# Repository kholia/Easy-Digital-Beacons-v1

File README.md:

### Easy-Digital-Beacons-v1

A simple and easy WiFi-enabled ESP8266-powered WSPR, FT8, and FT4 beacon system
which uses NTP + DS3231 RTC for timing. Also, checkout our [cost-effective, and
robust HF 5W PA system](https://github.com/kholia/HF-PA-v5/).

It is also a WiFi-enabled VFO, which is quite useful, and convenient for radio
experimentation work.

Note: The whole project can be assembled on a breadboard (including the [250mW
amplifier](./QRPp-Amplifier)) in under 30 minutes - do give it a go ;)

The whole design is modular, parametric (cost and others), field repairable,
and super extensible. It is almost trivial to add support for more `beacon
modes`.

#### Build Steps

If you are using Windows OS, execute the following steps:

- Download this repository by [clicking here](https://github.com/kholia/Easy-Digital-Beacons-v1/archive/refs/heads/master.zip).

- Extract the downloaded zip file to a folder.

- Run the `setup_arduino_ide.bat` file inside this folder.

- Install https://github.com/me-no-dev/ESPAsyncWebServer library.

- Install https://github.com/me-no-dev/ESPAsyncTCP library.

If you are on Linux, execute the following steps:

```
sudo apt-get install git  # install 'git' if needed

git clone https://github.com/kholia/Easy-Digital-Beacons-v1.git

make install_arduino_cli
make install_platform
make deps  # using Windows?, read the 'Makefile' file

cd ~/Arduino/libraries
git clone https://github.com/me-no-dev/ESPAsyncWebServer.git
git clone https://github.com/me-no-dev/ESPAsyncTCP.git
```

Now execute these common steps:

Add your WiFi credentials in `Easy-Digital-Beacons-v4/credentials.h` file

Change the following lines in the code to use your values:

```
char message[] = "VU3CER VU3FOE MK68";
char call[] = "VU3FOE";
char loc[] = "MK68";
uint8_t dbm = 27;
```

[OPTIONAL] Change the following line in the code to suit your Si5351A module:

```
int32_t si5351CalibrationFactor =  ...
```

Use [this program](https://github.com/etherkit/Si5351Arduino/blob/master/examples/si5351_calibration/si5351_calibration.ino)
to derive the calibration value for your Si5351A module.

Follow [this tutorial first](https://randomnerdtutorials.com/esp8266-web-server-spiffs-nodemcu/) to
get familiar with `SPIFFS` uploading stuff. Use the `Tools -> ESP8266 Sketch
Data Upload` option in the Arduino IDE to upload the webserver resources to
ESP8266. Note: The webserver resources are located in the `data` folder
inside the `Easy-Digital-Beacons-v4` sketch.

Open and upload the `Easy-Digital-Beacons-v4` sketch to ESP8266 using the
`Sketch -> Upload` option in the Arduino IDE.

You are all set for the next step - congrats!

#### Usage

Turn off the `SW1` switch, and reboot the beacon system. The beacon system now
connects to your WiFi, and then runs a web server.

This web server can be accessed at http://beacon.local URL typically.

Beacon's web interface:

Use this web interface to configure the beacon. Please use the `NTP Sync`
option in this web interface to set the RTC time fairly correctly.

Now, turn on the `SW1` switch, and reboot the beacon system. The beacon system
is active now, and will TX as per the configuration.

TIP: Please use a local (or nearby) receiver to receive and decode the beacon
signals! This is important to ensure that your beacon is TX'ing correctly.

Si5351A module is connected via I2C to pins D1 (SCL) and D2 (SDA) of the Wemos
D1 Mini board. Connect DS3231 similarly.

Here is the schematic for the `Easy-Digital-Beacons-v4` sketch:

For troubleshooting, you may want to try the following similar project by the
awesome WB2CBA:

- https://antrak.org.tr/blog/esp-wspr-simple-and-inexpensive-wspr-transmitter/
- https://antrak.org.tr/blog/a-whisper-wspr-adventure-and-esp_wspr/

#### Notes

Note 2 (March-2022): The `FT4` beacon is decently reliable now (all thanks to
Anupam).

Author: Dhiru Kholia (VU3CER) - https://www.qrz.com/db/VU3CER/

Author 2: Anupam Saikia - https://github.com/anupamsaikia

The `DT` timings are very nice with `NTP Sync`, `DS3231 RTC` and the optional
`time-delta hack`.

7W (or less) of HF RF power offers global communications coverage when
propagation is good:

WSPR mode demo:

Sample 3D rendering:

FT4 mode demo:

FST4W mode demo:

#### Battery System Recommendation

I recommend using a LiFePo4 (LFP) battery which has good energy density and is
also priced decently well.

Use the LFP battery with a `1S LFP BMS`.

The BMS' output can be connected directly to the 3.3v input of the ESP8266
module.

#### NTP (Time) Sync for FST4W-Antonio

In the Arduino IDE, select `Tools -> Serial Monitor`. In the `Serial Monitor`
send `s` character to ESP8266 to trigger the `NTP Time Sync` process.

Reboot ESP8266 to check if RTC is retaining the correct time. If not, change
the RTC battery.

#### Power Notes

This will need a HF RF PA in most cases to be usable on the air.

UPDATE (May 2022): Checkout our [cost-effective, and robust HF PA system](https://github.com/kholia/HF-PA-v6/).

You can also start with the easy-to-build and breadboard-friendly [QRPp-Amplifier](./QRPp-Amplifier).

#### Relay Usage

We use a 2-channel relay as a `T/R switch`.

See https://github.com/kholia/Simple-TR-Switch for details.

Also check out https://github.com/kholia/Easy-Transceiver project.

#### BOM

- 1 x 3/5mm LED (purple or pink is recommended)

- 1 x small regular (spst) chassis mount switch

- 1 x 0.25w 470 ohm resistor (CFR / MFR)

- Relimate male connectors

- Relimate female-female cables

- Female berg strips

- Zero PCB of a suitable size

Si5351A Module:

DS3231 RTC Module:

μC Board:

OLED screen (optional):

#### BOM Sources

- https://robu.in/

- https://www.electronicscomp.com/

- https://projectpoint.in/

#### Tips

Useful commands:

```
pacmd load-module module-null-sink sink_name=Virtual0
pacmd update-sink-proplist Virtual0 device.description=Virtual0
pacmd update-source-proplist Virtual0.monitor device.description=Virtual0
```

Use Gqrx and WSJT-X with a SDR device for initial frequency adjustment /
calibration. This is essential for WSPR functionality. FT8 is more
robust/tolerant of frequency deviations due to a much larger RX window.

Note: To customize the FST4W beacon to use your callsign and grid, use the
following commands to generate the `FST4Wsymbols` array data.

```
fst4sim.exe "IK1HGI JN45 20" 60 1500 0.0 0.1 1.0 10 -15 F > message.txt

message2array.exe message.txt
```

Replace the original `FST4Wsymbols` array data with the output of
`message2array.exe` program.

#### Future Tasks

- Change Si5351 calibration factor from the Web UI

- Add support for custom FT8 / FT4 messages

- Re-announce mDNS stuff [LP]

- EEPROM - save TX interval / schedule [LP]

- Reset to defaults button [LP]

#### References + Credits

- https://github.com/kholia/Si5351-Module-Clone-TCXO/ (use this module - it rocks!)

- https://github.com/kholia/Easy-Transceiver

- https://github.com/kgoba/ft8_lib

- https://github.com/etherkit/JTEncode

- https://github.com/Naguissa/uEEPROMLib

- https://randomnerdtutorials.com/esp8266-web-server-spiffs-nodemcu/

- https://lastminuteengineers.com/ds3231-rtc-arduino-tutorial/

- https://learn.adafruit.com/adafruit-si5351-clock-generator-breakout/wiring-and-test

- https://github.com/agustinmartino/wsjt_transceiver

- https://github.com/agustinmartino/wsjtx_transceiver_interface

- https://www.qrp-labs.com/synth/ms5351m.html

- https://github.com/anupamsaikia - FT4 fixes - thanks!

- https://github.com/f4goh/WSPR (pretty cool)

- https://github.com/lu7did/PixiePi

- https://github.com/iw5ejm/multibandWSPR_nodeMCU

- https://km4nmp.com/2019/08/24/vfo-for-the-pixie-wiring-and-sketch-for-ad9850/

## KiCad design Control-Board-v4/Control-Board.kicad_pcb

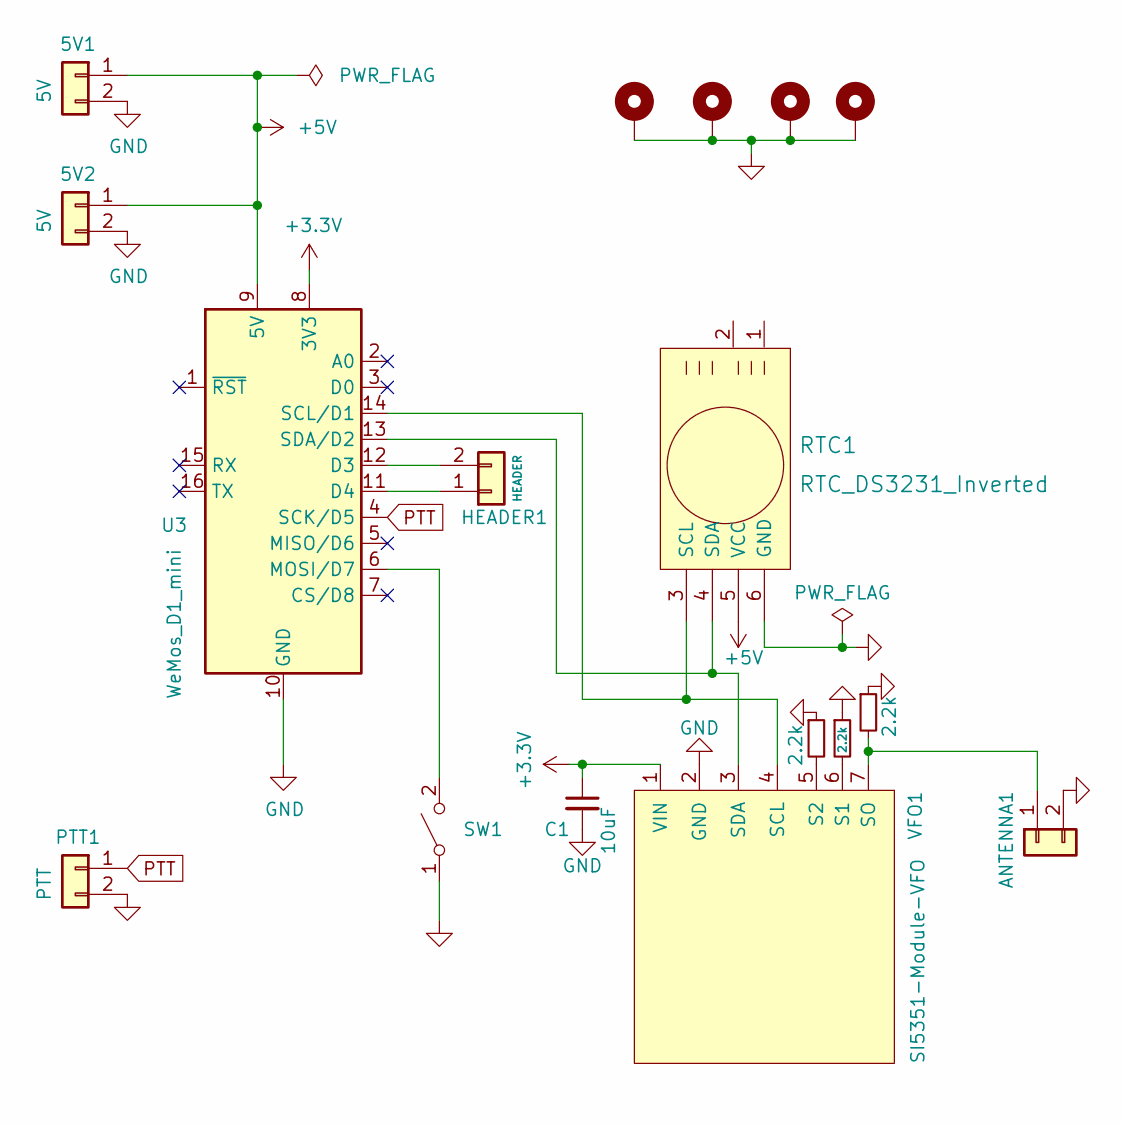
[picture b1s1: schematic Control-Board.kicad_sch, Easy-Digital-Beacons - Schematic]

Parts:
5V1, 5V2: 5V; PinHeader_1x02_P2.54mm_Vertical
ANTENNA1: ANTENNA; TerminalBlock_bornier-2_P5.08mm
C1: 10uF; C_1206_3216Metric_Pad1.33x1.80mm_HandSolder
H1, H2, H3, H4: MountingHole; MountingHole_2.2mm_M2_Pad
HEADER1: HEADER; PinHeader_1x02_P2.54mm_Vertical
PTT1: PTT; PinHeader_1x02_P2.54mm_Vertical
R1, R2, R3: 2.2k; R_1206_3216Metric_Pad1.30x1.75mm_HandSolder
RTC1: RTC_DS3231_Inverted; PinSocket_1x06_P2.54mm_Horizontal
SW1: SW_SPST; PinHeader_1x02_P2.54mm_Vertical
U3: WeMos_D1_mini; WEMOS_D1_mini_light
VFO1: SI5351-Module-VFO; PinSocket_1x07_P2.54mm_Vertical

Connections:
+3.3V: C1.1, U3.8 (3V3), VFO1.1 (VIN)
+5V: 5V1.1, 5V2.1, RTC1.5 (VCC), U3.9 (5V)
GND: 5V1.2, 5V2.2, ANTENNA1.2, C1.2, H1.1, H2.1, H3.1, H4.1, PTT1.2, R1.1, R2.1, R3.1, RTC1.6 (GND), SW1.1 (A), U3.10 (GND), VFO1.2 (GND)
unnamed: ANTENNA1.1, R3.2, VFO1.7 (SO)
unnamed: HEADER1.1, U3.11 (D4)
unnamed: HEADER1.2, U3.12 (D3)
unnamed: RTC1.3 (SCL), U3.14 (SCL/D1), VFO1.4 (SCL)
unnamed: RTC1.4 (SDA), U3.13 (SDA/D2), VFO1.3 (SDA)
unnamed: SW1.2 (B), U3.6 (MOSI/D7)
unnamed: R2.2, VFO1.6 (S1)
unnamed: R1.2, VFO1.5 (S2)
PTT: PTT1.1, U3.4 (SCK/D5)

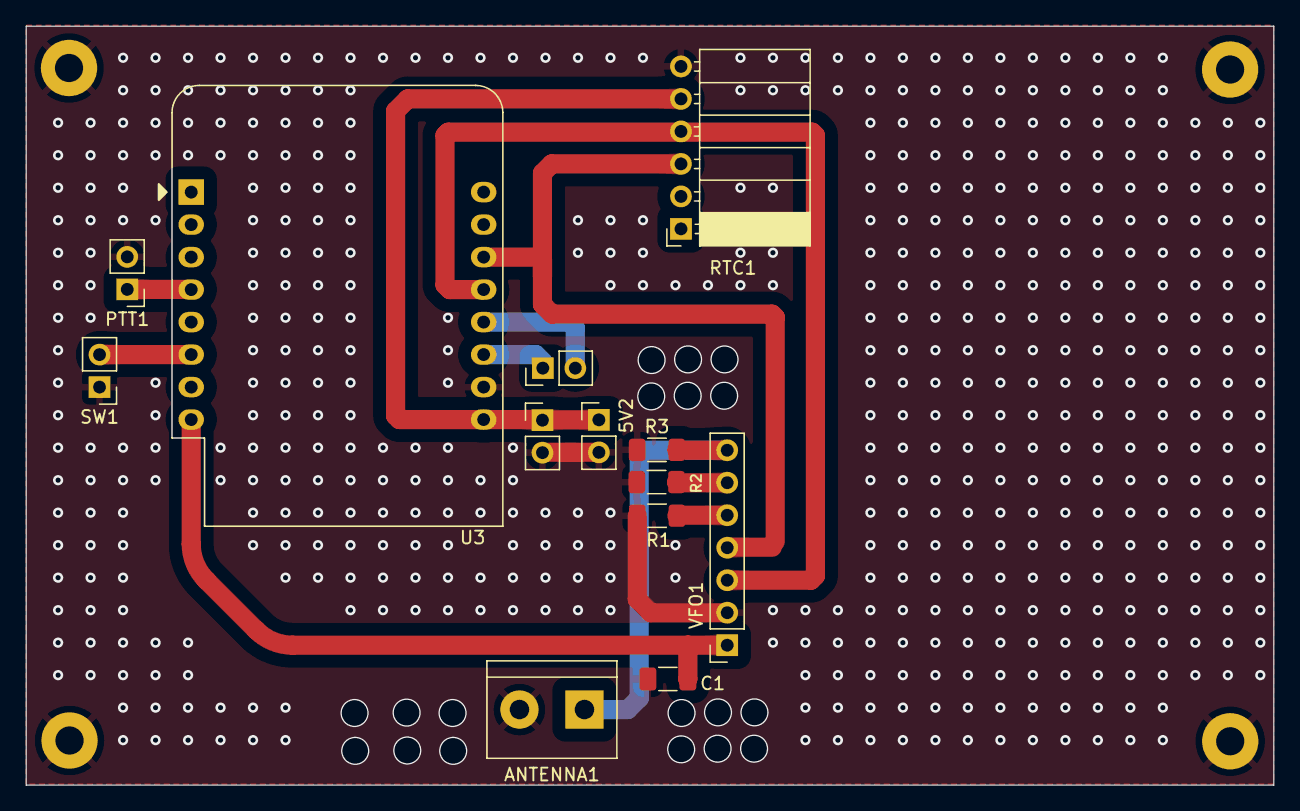
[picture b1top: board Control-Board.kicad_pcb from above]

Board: 2 copper layers, 97.5 x 59.3 mm, 17 parts (0 on the bottom side), 12 nets.

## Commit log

2022-07-23 Hello!
2023-10-02 Add support for 'Custom WSPR messages'
